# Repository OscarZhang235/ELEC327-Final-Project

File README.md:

# MagicKeyboard - ELEC327 Final Project

This is the official repository for **MagicKeyboard**, a low-power embedded system project developed for ELEC327 at Rice University.

## Team Members
- Oscar Zhang  
- Gerald Lu  
- Kerry Xu

## Project Overview
MagicKeyboard is a motion- and touch-responsive embedded device that mimics a keyboard using the TI MSPM0 microcontroller. It utilizes real-time processing, low-power design principles, and external sensors to create an intuitive input experience.

## Contents
- `index.html`: Website homepage with embedded videos and downloadable files
- `/static/`: Contains stylesheets, PDFs, videos, and other media assets
- `/code/`: Source code for the embedded system (main program, headers, drivers)
- `MagicKeyboard_Final_Report.pdf`: Lab report summarizing the project concept, implementation, and results

## Links
- [Live Website](https://oscarzhang235.github.io/ELEC327-Final-Project1/)

## License
This project uses the [Academic Project Page Template](https://github.com/eliahuhorwitz/Academic-project-page-template). All code and materials are provided for educational use only.

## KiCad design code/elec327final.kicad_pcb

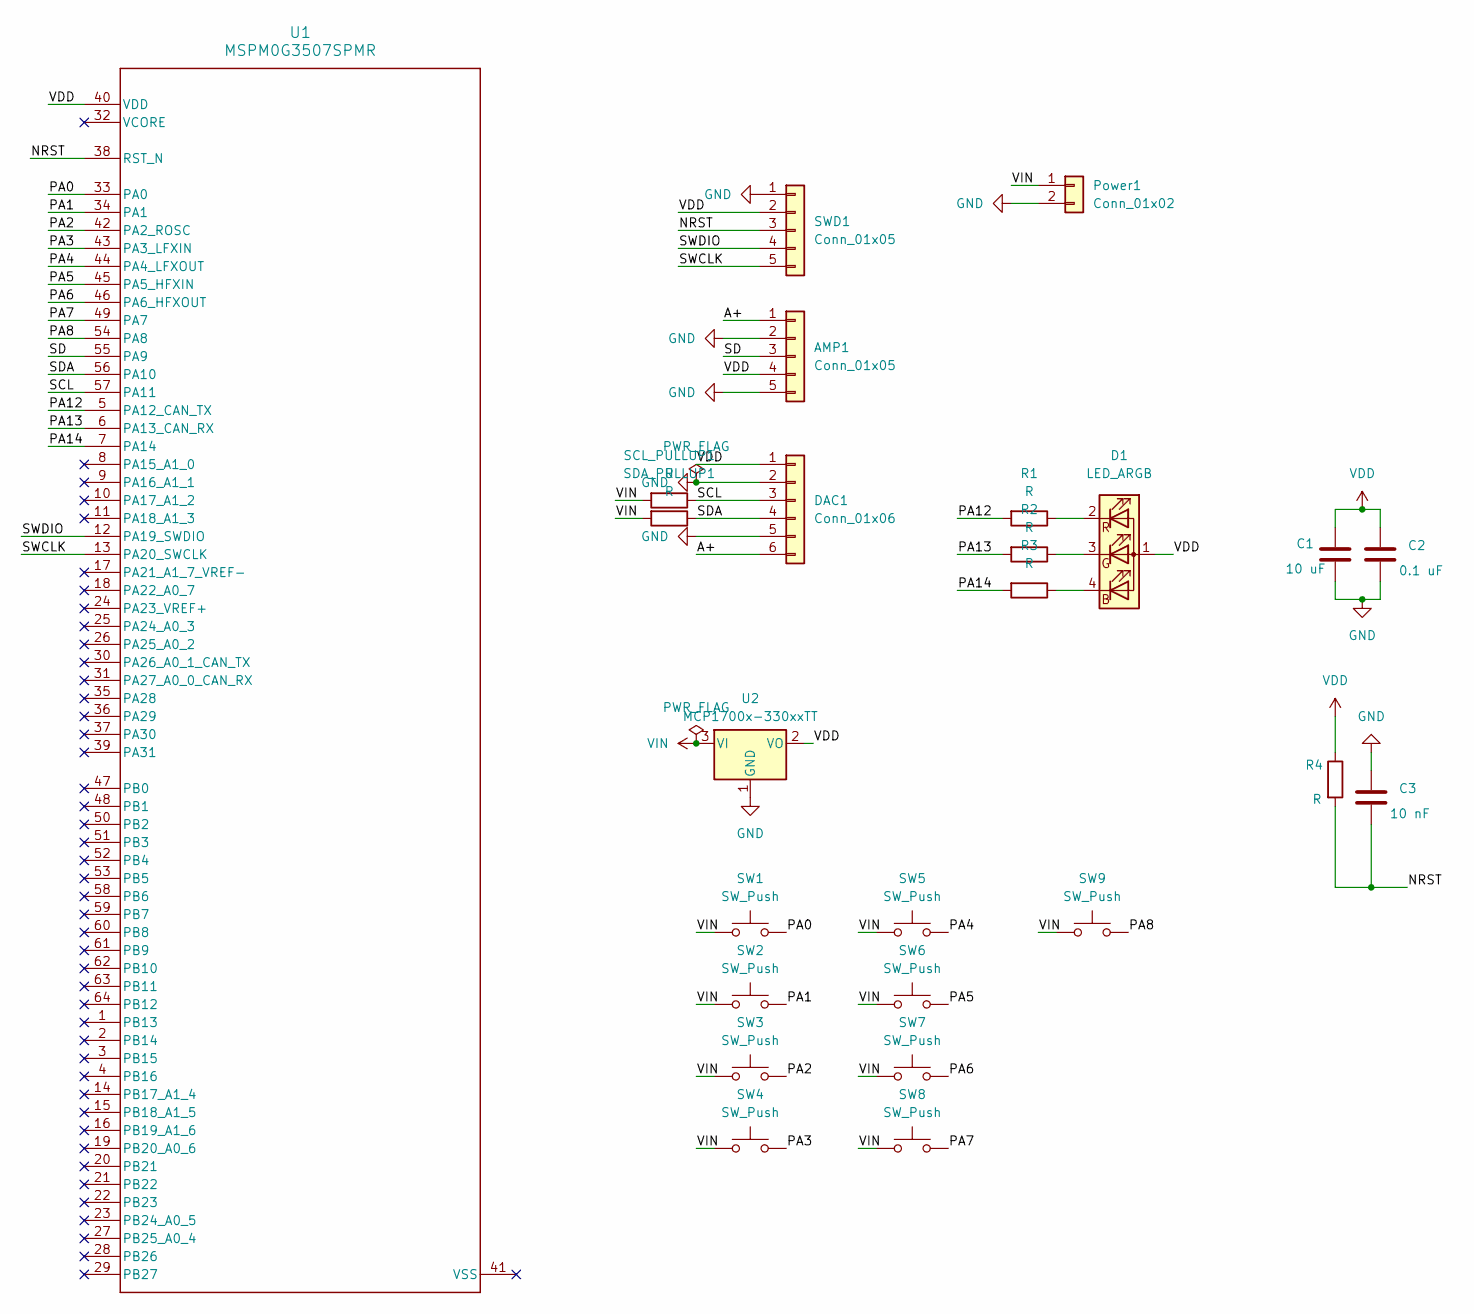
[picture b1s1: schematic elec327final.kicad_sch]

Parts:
AMP1: Conn_01x05; PinHeader_1x05_P2.54mm_Horizontal
C1: 10 uF; C_1210_3225Metric_Pad1.33x2.70mm_HandSolder
C2: 0.1 uF; C_0805_2012Metric_Pad1.18x1.45mm_HandSolder
C3: 10 nF; C_0805_2012Metric_Pad1.18x1.45mm_HandSolder
D1: LED_ARGB; LED_RGB_1210
DAC1: Conn_01x06; PinHeader_1x06_P2.54mm_Horizontal
Power1: Conn_01x02; PinHeader_1x02_P2.54mm_Horizontal
R1, R2, R3, R4: R; R_0805_2012Metric_Pad1.20x1.40mm_HandSolder
SCL_PULLUP1: R; R_0805_2012Metric_Pad1.20x1.40mm_HandSolder
SDA_PULLUP1: R; R_0805_2012Metric_Pad1.20x1.40mm_HandSolder
SW1, SW2, SW3, SW4, SW5, SW6, SW7, SW8, SW9: SW_Push; SW_PUSH_6mm_H5mm
SWD1: Conn_01x05; PinHeader_1x05_P2.54mm_Horizontal
U1: MSPM0G3507SPMR; PM0064A-IPC_A
U2: MCP1700x-330xxTT; SOT-23

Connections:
/A+: AMP1.1, DAC1.6
/NRST: C3.2, R4.2, SWD1.3, U1.38 (RST_N)
/PA0: SW1.2, U1.33 (PA0)
/PA1: SW2.2, U1.34 (PA1)
/PA2: SW3.2, U1.42 (PA2_ROSC)
/PA3: SW4.2, U1.43 (PA3_LFXIN)
/PA4: SW5.2, U1.44 (PA4_LFXOUT)
/PA5: SW6.2, U1.45 (PA5_HFXIN)
/PA6: SW7.2, U1.46 (PA6_HFXOUT)
/PA7: SW8.2, U1.49 (PA7)
/PA8: SW9.2, U1.54 (PA8)
/PA12: R1.2, U1.5 (PA12_CAN_TX)
/PA13: R2.2, U1.6 (PA13_CAN_RX)
/PA14: R3.2, U1.7 (PA14)
/SCL: DAC1.3, SCL_PULLUP1.1, U1.57 (PA11)
/SD: AMP1.3, U1.55 (PA9)
/SDA: DAC1.4, SDA_PULLUP1.1, U1.56 (PA10)
/SWCLK: SWD1.5, U1.13 (PA20_SWCLK)
/SWDIO: SWD1.4, U1.12 (PA19_SWDIO)
GND: AMP1.2, AMP1.5, C1.2, C2.2, C3.1, DAC1.2, DAC1.5, Power1.2, SWD1.1, U2.1 (GND)
unnamed: D1.4 (BK), R3.1
unnamed: D1.3 (GK), R2.1
unnamed: D1.2 (RK), R1.1
VDD: AMP1.4, C1.1, C2.1, D1.1 (A), DAC1.1, R4.1, SWD1.2, U1.40 (VDD), U2.2 (VO)
VIN: Power1.1, SCL_PULLUP1.2, SDA_PULLUP1.2, SW1.1, SW2.1, SW3.1, SW4.1, SW5.1, SW6.1, SW7.1, SW8.1, SW9.1, U2.3 (VI)

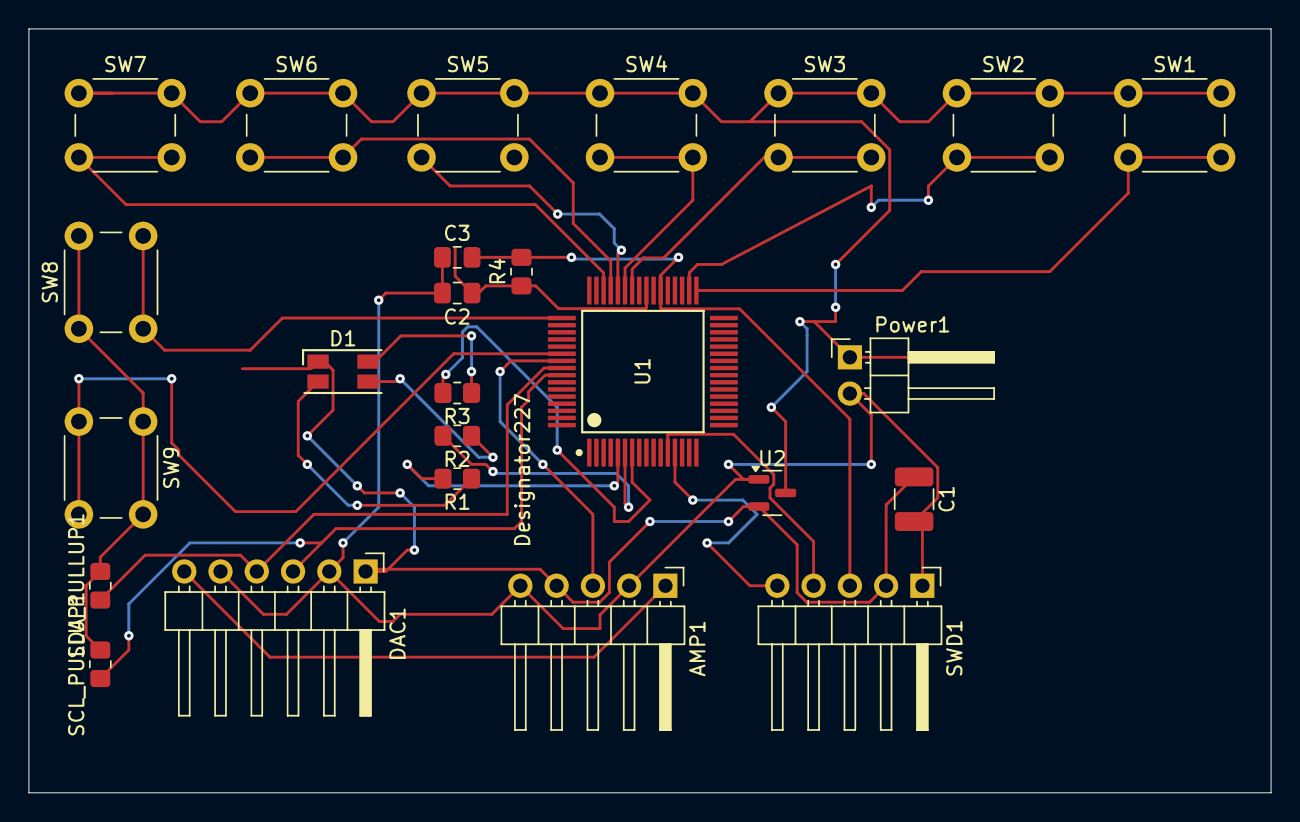
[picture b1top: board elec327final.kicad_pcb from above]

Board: 2 copper layers, 87.0 x 53.5 mm, 25 parts (0 on the bottom side), 25 nets.

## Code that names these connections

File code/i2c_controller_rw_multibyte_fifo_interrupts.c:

#include "ti_msp_dl_config.h"

#define DAC_ADDR            0x62
#define SD_PIN              DL_GPIO_PIN_9    /* PA9 = MCP4725 SD */
#define LED_PIN             DL_GPIO_PIN_13   /* PA13 = debug LED */

#define SW0_PIN             DL_GPIO_PIN_0    /* PA0 */
#define SW1_PIN             DL_GPIO_PIN_1    /* PA1 */
#define SW2_PIN             DL_GPIO_PIN_2    /* PA2 */
#define SW3_PIN             DL_GPIO_PIN_3    /* PA3 */
#define SW4_PIN             DL_GPIO_PIN_4    /* PA4 */
#define SW5_PIN             DL_GPIO_PIN_5    /* PA5 */
#define SW6_PIN             DL_GPIO_PIN_6    /* PA6 */

#define TONE_HIGH           4095U            /* full‑scale high = 3.3 V */
#define TONE_LOW                0U            /* full‑scale low  = 0 V */
#define SILENCE             2048U            /* mid‑scale = silence */

#define HALF_PERIOD_DELAYS0  6000U           /* highest freq */
#define HALF_PERIOD_DELAYS1  7000U
#define HALF_PERIOD_DELAYS2  8000U
#define HALF_PERIOD_DELAYS3  9000U
#define HALF_PERIOD_DELAYS4 10000U
#define HALF_PERIOD_DELAYS5 11000U
#define HALF_PERIOD_DELAYS6 12000U           /* lowest freq */

static inline void dac_write(uint16_t v)
{
    uint8_t buf[2] = { (uint8_t)(v >> 4), (uint8_t)(v << 4) };
    while (!(DL_I2C_getControllerStatus(I2C_0_INST) &
             DL_I2C_CONTROLLER_STATUS_IDLE)) { }
    DL_I2C_fillControllerTXFIFO(I2C_0_INST, buf, 2);
    DL_I2C_startControllerTransfer(I2C_0_INST,
                                   DAC_ADDR, 2, false);
    while (!(DL_I2C_getControllerStatus(I2C_0_INST) &
             DL_I2C_CONTROLLER_STATUS_IDLE)) { }
}

int main(void)
{
    SYSCFG_DL_init();  // sets up I²C_0, PA0–PA6 inputs, PA9/PA13 outputs

    // Ensure MCP4725 SD pin is high so the DAC is always enabled
    DL_GPIO_enableOutput(GPIOA, SD_PIN);
    DL_GPIO_setPins    (GPIOA, SD_PIN);

    // LED debug pin (PA13)
    DL_GPIO_enableOutput(GPIOA, LED_PIN);
    DL_GPIO_clearPins (GPIOA, LED_PIN);  // start OFF

    bool tone0 = false, tone1 = false, tone2 = false,
         tone3 = false, tone4 = false, tone5 = false, tone6 = false;

    while (1) {
        // 1) read all seven buttons
        bool p0 = (DL_GPIO_readPins(GPIOA, SW0_PIN) & SW0_PIN) != 0;
        bool p1 = (DL_GPIO_readPins(GPIOA, SW1_PIN) & SW1_PIN) != 0;
        bool p2 = (DL_GPIO_readPins(GPIOA, SW2_PIN) & SW2_PIN) != 0;
        bool p3 = (DL_GPIO_readPins(GPIOA, SW3_PIN) & SW3_PIN) != 0;
        bool p4 = (DL_GPIO_readPins(GPIOA, SW4_PIN) & SW4_PIN) != 0;
        bool p5 = (DL_GPIO_readPins(GPIOA, SW5_PIN) & SW5_PIN) != 0;
        bool p6 = (DL_GPIO_readPins(GPIOA, SW6_PIN) & SW6_PIN) != 0;

        // 2) mirror any press on the LED
        if (p0 || p1 || p2 || p3 || p4 || p5 || p6)
            DL_GPIO_setPins  (GPIOA, LED_PIN);
        else
            DL_GPIO_clearPins(GPIOA, LED_PIN);

        // 3) generate the tone for the first pressed switch
        if (p0) {
            tone0 = !tone0;
            dac_write(tone0 ? TONE_HIGH : TONE_LOW);
            for (volatile uint32_t i = 0; i < HALF_PERIOD_DELAYS0; ++i) { }
        }
        else if (p1) {
            tone1 = !tone1;
            dac_write(tone1 ? TONE_HIGH : TONE_LOW);
            for (volatile uint32_t i = 0; i < HALF_PERIOD_DELAYS1; ++i) { }
        }
        else if (p2) {
            tone2 = !tone2;
            dac_write(tone2 ? TONE_HIGH : TONE_LOW);
            for (volatile uint32_t i = 0; i < HALF_PERIOD_DELAYS2; ++i) { }
        }
        else if (p3) {
            tone3 = !tone3;
            dac_write(tone3 ? TONE_HIGH : TONE_LOW);
            for (volatile uint32_t i = 0; i < HALF_PERIOD_DELAYS3; ++i) { }
        }
        else if (p4) {
            tone4 = !tone4;
            dac_write(tone4 ? TONE_HIGH : TONE_LOW);
            for (volatile uint32_t i = 0; i < HALF_PERIOD_DELAYS4; ++i) { }
        }
        else if (p5) {
            tone5 = !tone5;
            dac_write(tone5 ? TONE_HIGH : TONE_LOW);
            for (volatile uint32_t i = 0; i < HALF_PERIOD_DELAYS5; ++i) { }
        }
        else if (p6) {
            tone6 = !tone6;
            dac_write(tone6 ? TONE_HIGH : TONE_LOW);
            for (volatile uint32_t i = 0; i < HALF_PERIOD_DELAYS6; ++i) { }
        }
        else {
            // no key pressed → silence
            dac_write(SILENCE);
        }
    }

    // never reached
    return 0;
}

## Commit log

2025-05-05 Create code
